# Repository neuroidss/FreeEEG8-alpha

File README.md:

# FreeEEG8-alpha

[mobile_diagnostic_stand](https://neuroidss.github.io/FreeEEG8-alpha/semantic_engine/mobile_diagnostic_stand.html)

[Neuro-Arena_Anonymous_Nodes](https://neuroidss.github.io/FreeEEG8-alpha/neuro_game/Neuro-Arena_Anonymous_Nodes.html)

[neuro_dungeon_gamepad_emulator_mimic](https://neuroidss.github.io/FreeEEG8-alpha/neuro_game/neuro_dungeon_gamepad_emulator_mimic.html)

[neuro_dungeon_gamepad_emulator_crystal](https://neuroidss.github.io/FreeEEG8-alpha/neuro_game/neuro_dungeon_gamepad_emulator_crystal.html)

[neuro_dungeon_gamepad_emulator_dash](https://neuroidss.github.io/FreeEEG8-alpha/neuro_game/neuro_dungeon_gamepad_emulator_dash.html)

[neuro_dungeon_gamepad_emulator_wm](https://neuroidss.github.io/FreeEEG8-alpha/neuro_game/neuro_dungeon_gamepad_emulator_wm.html)

[neuro_dungeon_gamepad_emulator_vr](https://neuroidss.github.io/FreeEEG8-alpha/neuro_game/neuro_dungeon_gamepad_emulator_vr.html)

[neuro_dungeon_emulator](https://neuroidss.github.io/FreeEEG8-alpha/neuro_game/neuro_dungeon_emulator.html)

[neuro_dungeon_dual_stick](https://neuroidss.github.io/FreeEEG8-alpha/neuro_game/neuro_dungeon_dual_stick.html)

[neuro_dungeon_cyber](https://neuroidss.github.io/FreeEEG8-alpha/neuro_game/neuro_dungeon_cyber.html)

[neuro_dungeon_joystick](https://neuroidss.github.io/FreeEEG8-alpha/neuro_game/neuro_dungeon_joystick.html)

[neuro_dungeon_4_wills](https://neuroidss.github.io/FreeEEG8-alpha/neuro_game/neuro_dungeon_4_wills.html)

[neuro_dungeon](https://neuroidss.github.io/FreeEEG8-alpha/neuro_game/neuro_dungeon.html)

[Emergent_Psytrance](https://neuroidss.github.io/FreeEEG8-alpha/psytrance/Emergent_Psytrance.html)

[Motor_Imagery_Web-Synth](https://neuroidss.github.io/FreeEEG8-alpha/psytrance/Motor_Imagery_Web-Synth.html)

[Neuro_Test_Bench](https://neuroidss.github.io/FreeEEG8-alpha/Neuro_Test_Bench/Neuro_Test_Bench.html)

[FreeEEG8-alpha_1_4_gerbers](https://github.com/neuroidss/FreeEEG8-alpha/releases/tag/FreeEEG8-alpha_1_4_gerbers)

run colab to get gerber&bom freeeeg8-alpha.kicad_pcb.zip

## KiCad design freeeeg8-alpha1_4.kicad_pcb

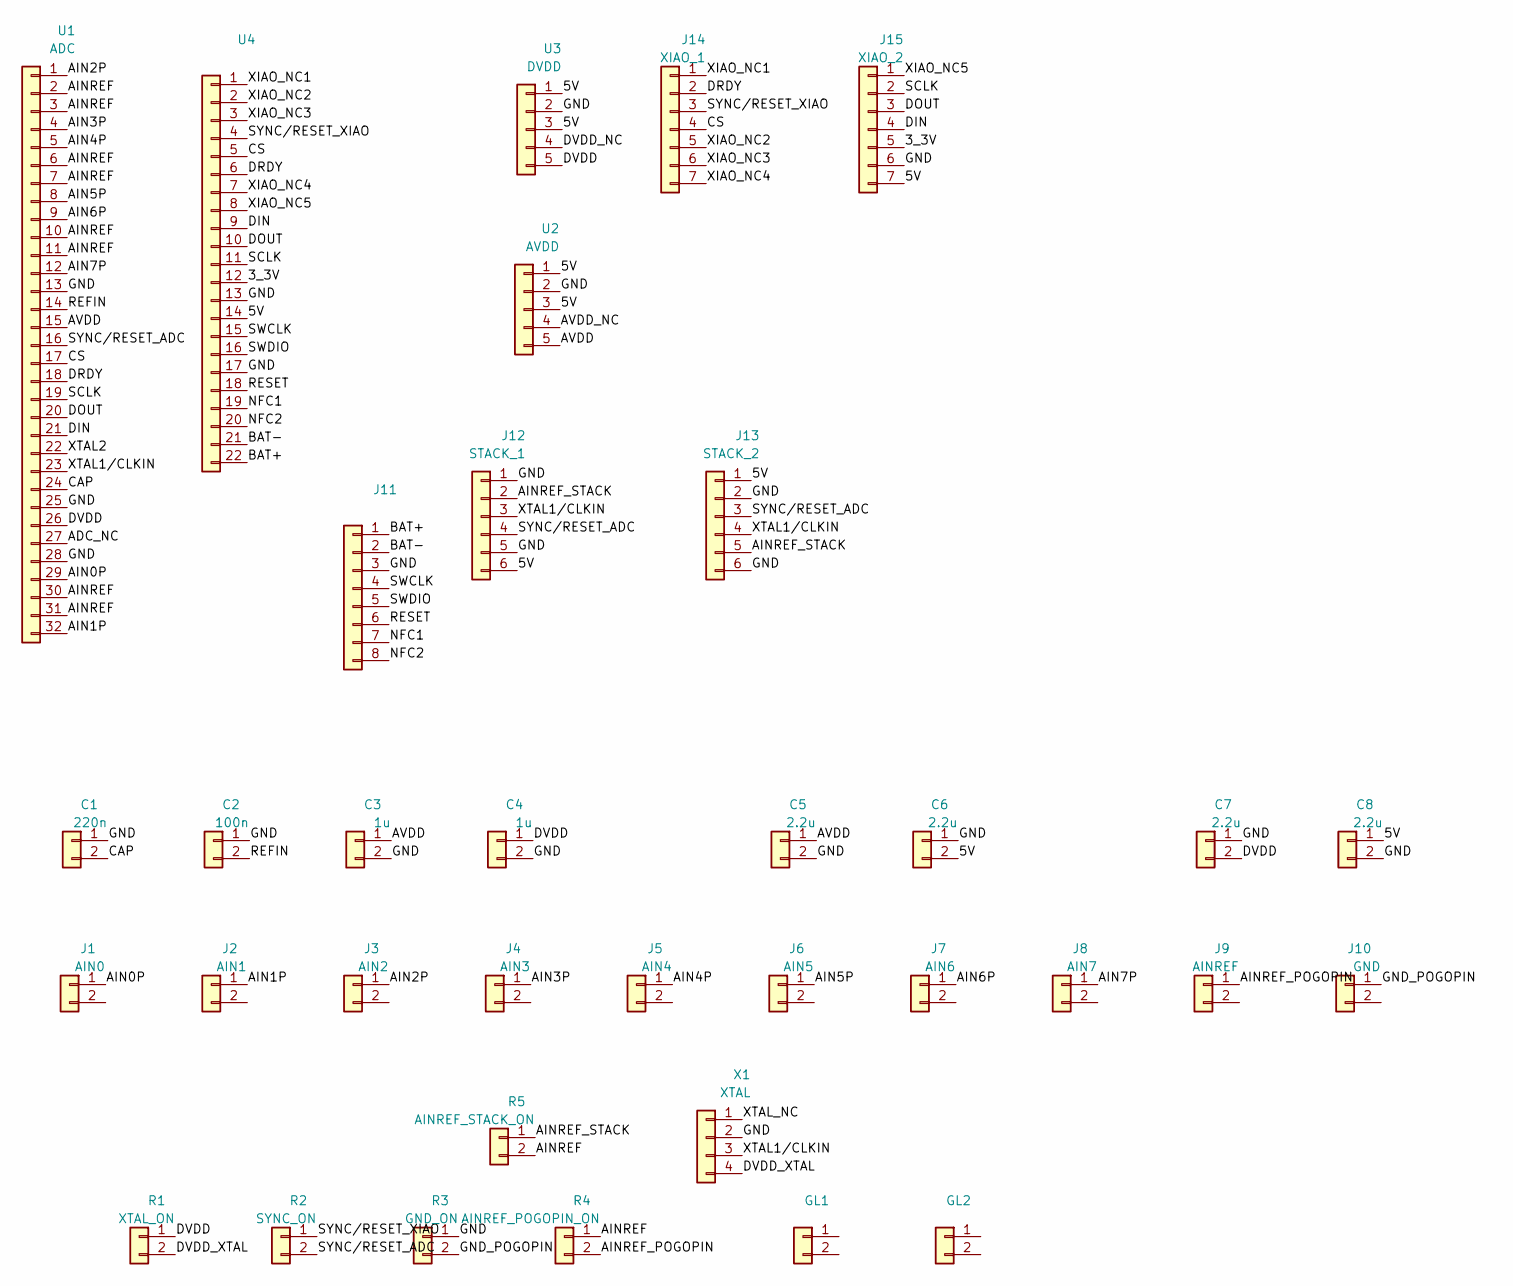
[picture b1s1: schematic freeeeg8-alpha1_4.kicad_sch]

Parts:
C1: 220n; C_0402_1005Metric; MPN CC0402KRX5R5BB224
C2: 100n; C_0402_1005Metric; MPN CL05B104KO5NNNC
C3, C4: 1u; C_0402_1005Metric; MPN CL05A105KO5NNNC
C5, C6, C7, C8: 2.2u; C_0603_1608Metric; MPN GRM188R71A225KE15D
GL1: FreeEEG8-alpha-title_5mm_SilkScreen
GL2: NeuroIDSS-url_5mm_SilkScreen
J1: AIN0; pogo_pin_d5x10mm_smd; MPN pogo-pin-d5x10mm-smd
J2: AIN1; pogo_pin_d5x10mm_smd; MPN pogo-pin-d5x10mm-smd
J3: AIN2; pogo_pin_d5x10mm_smd; MPN pogo-pin-d5x10mm-smd
J4: AIN3; pogo_pin_d5x10mm_smd; MPN pogo-pin-d5x10mm-smd
J5: AIN4; pogo_pin_d5x10mm_smd; MPN pogo-pin-d5x10mm-smd
J6: AIN5; pogo_pin_d5x10mm_smd; MPN pogo-pin-d5x10mm-smd
J7: AIN6; pogo_pin_d5x10mm_smd; MPN pogo-pin-d5x10mm-smd
J8: AIN7; pogo_pin_d5x10mm_smd; MPN pogo-pin-d5x10mm-smd
J9: AINREF; pogo_pin_d5x10mm_smd; MPN pogo-pin-d5x10mm-smd
J10: GND; pogo_pin_d5x10mm_smd; MPN pogo-pin-d5x10mm-smd
J11: Molex_PicoBlade_53398-0871_1x08-1MP_P1.25mm_Vertical_DNP
J12: STACK_1; Molex_PicoBlade_53398-0671_1x06-1MP_P1.25mm_Vertical_DNP; MPN 53398-0671
J13: STACK_2; Molex_PicoBlade_53398-0671_1x06-1MP_P1.25mm_Vertical_DNP; MPN 53398-0671
J14: XIAO_1; PinHeader_1x07_P2.54mm_Vertical_SMD_Pin1Right; MPN TSM-107-01-L-SV
J15: XIAO_2; PinHeader_1x07_P2.54mm_Vertical_SMD_Pin1Right; MPN TSM-107-01-L-SV
R1: XTAL_ON; R_0402_1005Metric; MPN RC0402JR-070RL
R2: SYNC_ON; R_0402_1005Metric; MPN RC0402JR-070RL
R3: GND_ON; R_0402_1005Metric; MPN RC0402JR-070RL
R4: AINREF_POGOPIN_ON; R_0402_1005Metric; MPN RC0402JR-070RL
R5: AINREF_STACK_ON; R_0402_1005Metric; MPN DNP
U1: ADC; LQFP-32_5x5mm_P0.5mm; MPN ADS131M08IPBSR
U2: AVDD; SOT-23-5; MPN LP5907QMFX-3.3Q1
U3: DVDD; SOT-23-5; MPN LP5907QMFX-3.3Q1
U4: XIAO-nRF52840-Sense-14P-2.54-21X17.8MM
X1: XTAL; Oscillator_SMD_EuroQuartz_XO32-4Pin_3.2x2.5mm_HandSoldering; MPN ECS-2520MVLC-081.92-CN-TR

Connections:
/3_3V: J15.5, U4.12
/5V: C6.2, C8.1, J12.6, J13.1, J15.7, U2.1, U2.3, U3.1, U3.3, U4.14
/ADC_NC: U1.27
/AIN0P: J1.1, U1.29
/AIN1P: J2.1, U1.32
/AIN2P: J3.1, U1.1
/AIN3P: J4.1, U1.4
/AIN4P: J5.1, U1.5
/AIN5P: J6.1, U1.8
/AIN6P: J7.1, U1.9
/AIN7P: J8.1, U1.12
/AINREF: R4.1, R5.2, U1.2, U1.3, U1.6, U1.7, U1.10, U1.11, U1.30, U1.31
/AINREF_POGOPIN: J9.1, R4.2
/AINREF_STACK: J12.2, J13.5, R5.1
/AVDD: C3.1, C5.1, U1.15, U2.5
/AVDD_NC: U2.4
/CAP: C1.2, U1.24
/CS: J14.4, U1.17, U4.5
/DIN: J15.4, U1.21, U4.9
/DOUT: J15.3, U1.20, U4.10
/DRDY: J14.2, U1.18, U4.6
/DVDD: C4.1, C7.2, R1.1, U1.26, U3.5
/DVDD_NC: U3.4
/DVDD_XTAL: R1.2, X1.4
/GND: C1.1, C2.1, C3.2, C4.2, C5.2, C6.1, C7.1, C8.2, J11.3, J12.1, J12.5, J13.2, J13.6, J15.6, R3.1, U1.13, U1.25, U1.28, U2.2, U3.2, U4.13, U4.17, X1.2
/GND_POGOPIN: J10.1, R3.2
/REFIN: C2.2, U1.14
/SCLK: J15.2, U1.19, U4.11
/SYNC/RESET_ADC: J12.4, J13.3, R2.2, U1.16
/SYNC/RESET_XIAO: J14.3, R2.1, U4.4
/XIAO_NC1: J14.1, U4.1
/XIAO_NC2: J14.5, U4.2
/XIAO_NC3: J14.6, U4.3
/XIAO_NC4: J14.7, U4.7
/XIAO_NC5: J15.1, U4.8
/XTAL1/CLKIN: J12.3, J13.4, U1.23, X1.3
/XTAL2: U1.22
/XTAL_NC: X1.1
unnamed: J11.1, U4.22
unnamed: J11.2, U4.21
unnamed: J11.4, U4.15
unnamed: J11.5, U4.16
unnamed: J11.6, U4.18
unnamed: J11.7, U4.19
unnamed: J11.8, U4.20

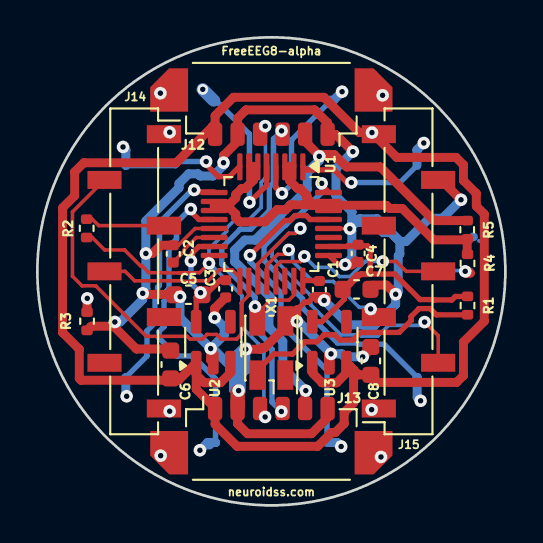
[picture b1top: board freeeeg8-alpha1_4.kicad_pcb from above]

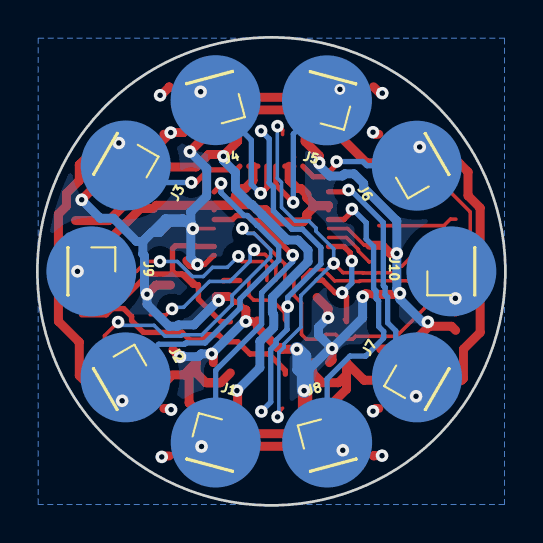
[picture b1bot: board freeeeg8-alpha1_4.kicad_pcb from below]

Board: 2 copper layers, 26.0 x 26.0 mm, 33 parts (10 on the bottom side), 27 nets.

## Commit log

2024-09-22 Создано в Colab
